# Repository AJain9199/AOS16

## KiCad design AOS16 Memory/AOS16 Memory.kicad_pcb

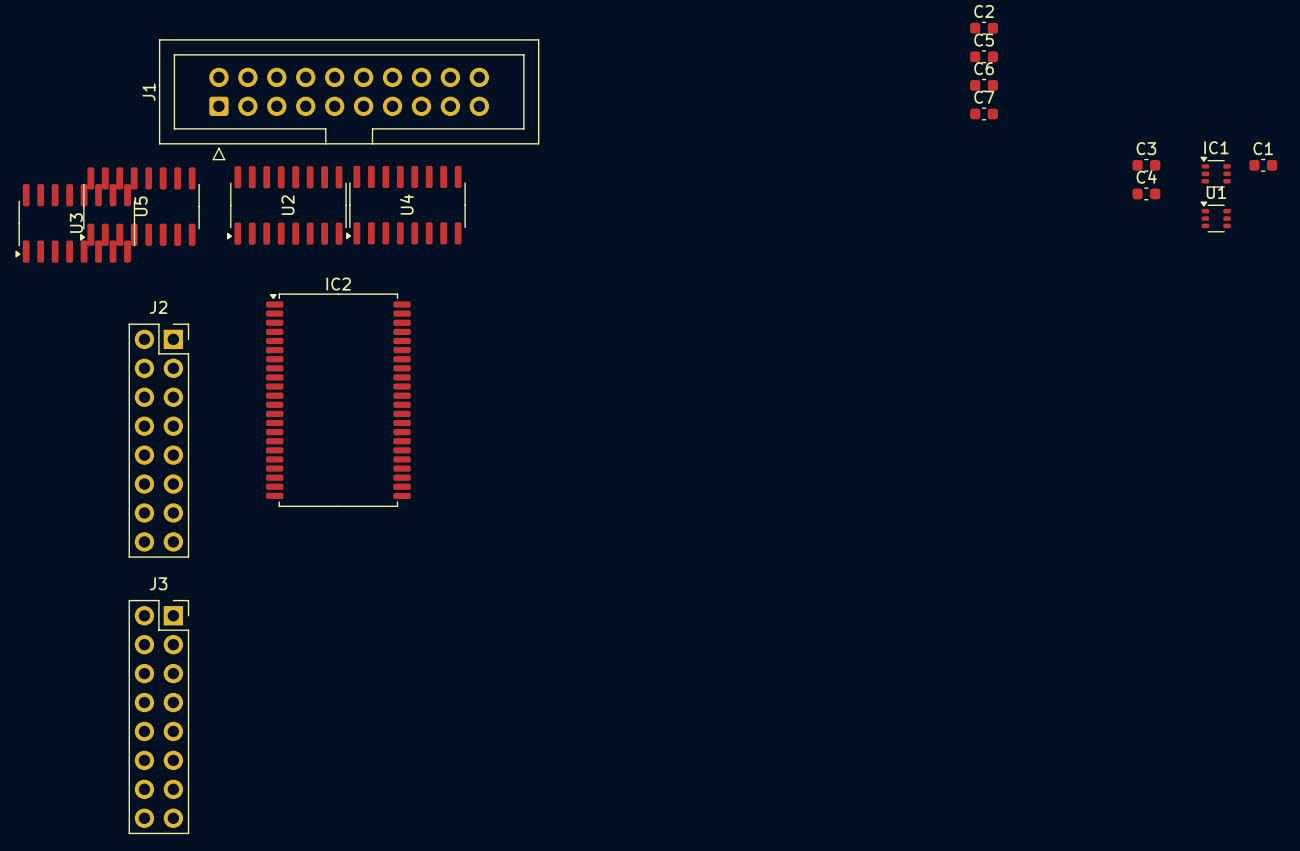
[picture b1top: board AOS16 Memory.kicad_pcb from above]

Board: 2 copper layers, 17 parts (0 on the bottom side), 39 nets, no tracks yet.

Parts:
C1, C2, C3, C4, C5, C6, C7: 0.1uF; C_0603_1608Metric
IC1: SN74AUP2G14DCKR; SOT-363_SC-70-6
IC2: IS61WV3216BLL-12TLI; TSOP-II-44_10.16x18.41mm_P0.8mm
J1: Conn_02x10_Odd_Even; IDC-Header_2x10_P2.54mm_Vertical
J2, J3: Conn_02x08_Top_Bottom; PinSocket_2x08_P2.54mm_Vertical
U1: 4081; SOT-363_SC-70-6
U2, U3, U4, U5: 74HC173; SOIC-16_3.9x9.9mm_P1.27mm

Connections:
/bus_conn/GND: J1.17, J1.19
/ram_chip/~OE: IC2.41 (~OE), U1.3
/register/CLK: J1.18, U2.7 (Cp), U3.7 (Cp), U4.7 (Cp), U5.7 (Cp)
/wordconn1/IN0: IC2.29 (I/O8), J1.1, J3.1, U3.14 (D0)
/wordconn1/IN1: IC2.16 (I/O7), J1.2, J3.2, U3.13 (D1)
/wordconn1/IN2: IC2.30 (I/O9), J1.3, J3.3, U3.12 (D2)
/wordconn1/IN3: IC2.7 (I/O0), J1.4, J3.4, U3.11 (D3)
/wordconn1/IN4: IC2.15 (I/O6), J1.5, J3.5, U5.14 (D0)
/wordconn1/IN5: IC2.8 (I/O1), J1.6, J3.6, U5.13 (D1)
/wordconn1/IN6: IC2.31 (I/O10), J1.7, J3.7, U5.12 (D2)
/wordconn1/IN7: IC2.38 (I/O15), J1.8, J3.8, U5.11 (D3)
/wordconn1/IN8: IC2.14 (I/O5), J1.9, J3.9, U2.14 (D0)
/wordconn1/IN9: IC2.9 (I/O2), J1.10, J3.10, U2.13 (D1)
/wordconn1/IN10: IC2.37 (I/O14), J1.11, J3.11, U2.12 (D2)
/wordconn1/IN11: IC2.32 (I/O11), J1.12, J3.12, U2.11 (D3)
/wordconn1/IN12: IC2.10 (I/O3), J1.13, J3.13, U4.14 (D0)
/wordconn1/IN13: IC2.13 (I/O4), J1.14, J3.14, U4.13 (D1)
/wordconn1/IN14: IC2.35 (I/O12), J1.15, J3.15, U4.12 (D2)
/wordconn1/IN15: IC2.36 (I/O13), J1.16, J3.16, U4.11 (D3)
/wordconn/IN0: IC2.44 (A0), J2.1, U3.3 (Q0)
/wordconn/IN1: IC2.2 (A14), J2.2, U3.4 (Q1)
/wordconn/IN2: IC2.21 (A7), J2.3, U3.5 (Q2)
/wordconn/IN3: IC2.43 (A1), J2.4, U3.6 (Q3)
/wordconn/IN4: IC2.24 (A6), J2.5, U5.3 (Q0)
/wordconn/IN5: IC2.3 (A13), J2.6, U5.4 (Q1)
/wordconn/IN6: IC2.20 (A8), J2.7, U5.5 (Q2)
/wordconn/IN7: IC2.42 (A2), J2.8, U5.6 (Q3)
/wordconn/IN8: IC2.25 (A5), J2.9, U2.3 (Q0)
/wordconn/IN9: IC2.4 (A12), J2.10, U2.4 (Q1)
/wordconn/IN10: IC2.19 (A9), J2.11, U2.5 (Q2)
/wordconn/IN11: IC2.5 (A11), J2.12, U2.6 (Q3)
/wordconn/IN12: IC2.26 (A4), J2.13, U4.3 (Q0)
/wordconn/IN13: IC2.27 (A3), J2.14, U4.4 (Q1)
/wordconn/IN14: IC2.18 (A10), J2.15, U4.5 (Q2)
/wordconn/IN15: IC1.3 (2A), J2.16, U4.6 (Q3)
/~DOUT15: IC1.4 (2Y), U1.1
/~MAI: IC1.6 (1Y), U2.9 (E1), U2.10 (E2), U3.9 (E1), U3.10 (E2), U4.9 (E1), U4.10 (E2), U5.9 (E1), U5.10 (E2)
GND: C1.1, C2.2, C3.2, C4.2, C5.2, C6.2, C7.2, IC1.2 (GND), IC2.6 (~CE), IC2.12 (GND_1), IC2.34 (GND_2), IC2.39 (~LB), IC2.40 (~UB), U2.1 (Oe1), U2.2 (Oe2), U2.8 (GND), U2.15 (Mr), U3.1 (Oe1), U3.2 (Oe2), U3.8 (GND), U3.15 (Mr), U4.1 (Oe1), U4.2 (Oe2), U4.8 (GND), U4.15 (Mr), U5.1 (Oe1), U5.2 (Oe2), U5.8 (GND), U5.15 (Mr)
VCC: C1.2, C2.1, C3.1, C4.1, C5.1, C6.1, C7.1, IC1.5 (VCC), IC2.11 (VDD_1), IC2.33 (VDD_2), U2.16 (VCC), U3.16 (VCC), U4.16 (VCC), U5.16 (VCC)

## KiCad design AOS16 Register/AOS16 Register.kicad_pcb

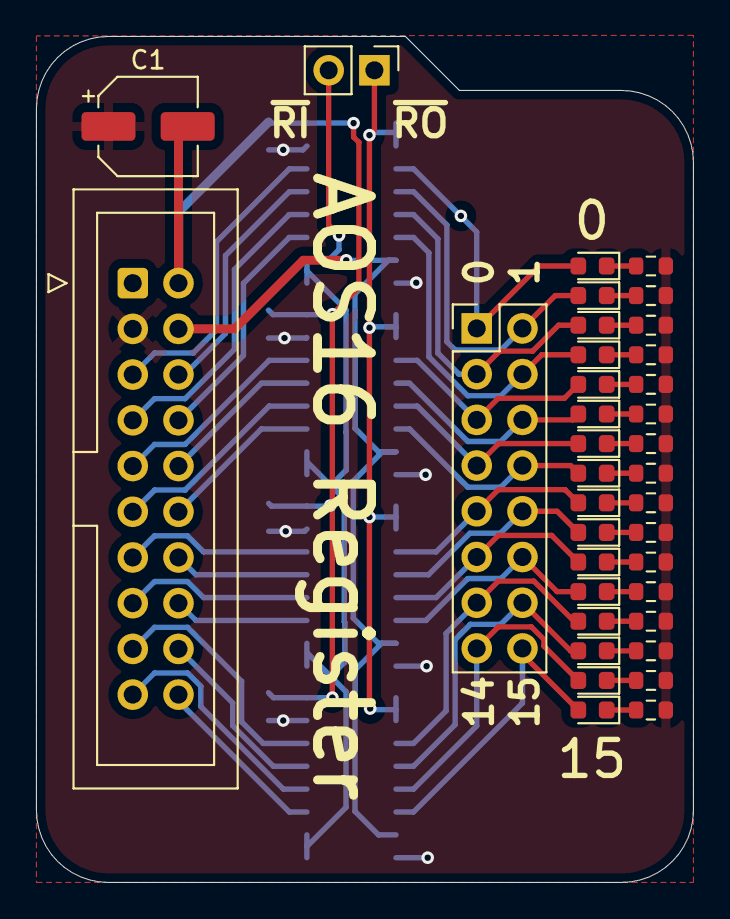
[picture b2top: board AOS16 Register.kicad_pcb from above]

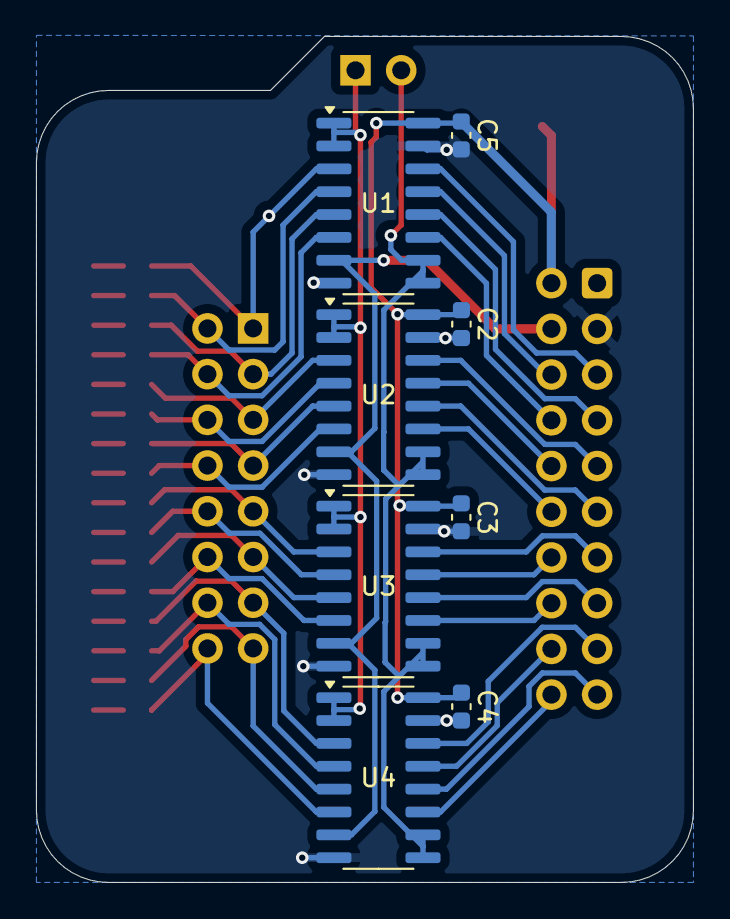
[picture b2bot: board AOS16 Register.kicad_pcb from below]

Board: 2 copper layers, 36.5 x 47.0 mm, 44 parts (8 on the bottom side), 53 nets.

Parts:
C1: 100uF; CP_Elec_5x5.3
C2, C3, C4, C5: 0.1uF; C_0603_1608Metric
D1, D2, D3, D4, D5, D6, D7, D8, D9, D10, D11, D12, D13, D14, D15, D16: LED; LED_0603_1608Metric
J1: Conn_01x02_Pin; PinHeader_1x02_P2.54mm_Vertical
J2: Conn_02x10_Odd_Even; IDC-Header_2x10_P2.54mm_Vertical
J3: Conn_02x08_Top_Bottom; PinHeader_2x08_P2.54mm_Vertical
R1, R2, R3, R4, R5, R6, R7, R8, R9, R10, R11, R12, R13, R14, R15, R16: R_Small; R_0603_1608Metric
U1, U2, U3, U4: 74HC173; SOIC-16_3.9x9.9mm_P1.27mm

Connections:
/CLK: J2.4, U1.7 (Cp), U2.7 (Cp), U3.7 (Cp), U4.7 (Cp)
/DOUT0: D1.2 (A), J3.1, U1.3 (Q0)
/DOUT1: D2.2 (A), J3.2, U1.4 (Q1)
/DOUT2: D3.2 (A), J3.3, U1.5 (Q2)
/DOUT3: D4.2 (A), J3.4, U1.6 (Q3)
/DOUT4: D5.2 (A), J3.5, U2.3 (Q0)
/DOUT5: D6.2 (A), J3.6, U2.4 (Q1)
/DOUT6: D7.2 (A), J3.7, U2.5 (Q2)
/DOUT7: D8.2 (A), J3.8, U2.6 (Q3)
/DOUT8: D9.2 (A), J3.9, U3.3 (Q0)
/DOUT9: D10.2 (A), J3.10, U3.4 (Q1)
/DOUT10: D11.2 (A), J3.11, U3.5 (Q2)
/DOUT11: D12.2 (A), J3.12, U3.6 (Q3)
/DOUT12: D13.2 (A), J3.13, U4.3 (Q0)
/DOUT13: D14.2 (A), J3.14, U4.4 (Q1)
/DOUT14: D15.2 (A), J3.15, U4.5 (Q2)
/DOUT15: D16.2 (A), J3.16, U4.6 (Q3)
/IO0: J2.5, U1.14 (D0)
/IO1: J2.6, U1.13 (D1)
/IO2: J2.7, U1.12 (D2)
/IO3: J2.8, U1.11 (D3)
/IO4: J2.9, U2.14 (D0)
/IO5: J2.10, U2.13 (D1)
/IO6: J2.11, U2.12 (D2)
/IO7: J2.12, U2.11 (D3)
/IO8: J2.13, U3.14 (D0)
/IO9: J2.14, U3.13 (D1)
/IO10: J2.15, U3.12 (D2)
/IO11: J2.16, U3.11 (D3)
/IO12: J2.17, U4.14 (D0)
/IO13: J2.18, U4.13 (D1)
/IO14: J2.19, U4.12 (D2)
/IO15: J2.20, U4.11 (D3)
/~IE: J1.2, U1.9 (E1), U1.10 (E2), U2.9 (E1), U2.10 (E2), U3.9 (E1), U3.10 (E2), U4.9 (E1), U4.10 (E2)
/~OE: J1.1, U1.1 (Oe1), U1.2 (Oe2), U2.1 (Oe1), U2.2 (Oe2), U3.1 (Oe1), U3.2 (Oe2), U4.1 (Oe1), U4.2 (Oe2)
GND: C1.1, C2.2, C3.2, C4.2, C5.2, J2.3, R1.2, R2.2, R3.2, R4.2, R5.2, R6.2, R7.2, R8.2, R9.2, R10.2, R11.2, R12.2, R13.2, R14.2, R15.2, R16.2, U1.8 (GND), U1.15 (Mr), U2.8 (GND), U2.15 (Mr), U3.8 (GND), U3.15 (Mr), U4.8 (GND), U4.15 (Mr)
unnamed: D1.1 (K), R1.1
unnamed: D2.1 (K), R2.1
unnamed: D3.1 (K), R3.1
unnamed: D4.1 (K), R4.1
unnamed: D5.1 (K), R5.1
unnamed: D6.1 (K), R6.1
unnamed: D7.1 (K), R7.1
unnamed: D8.1 (K), R8.1
unnamed: D9.1 (K), R9.1
unnamed: D10.1 (K), R10.1
unnamed: D11.1 (K), R11.1
unnamed: D12.1 (K), R12.1
unnamed: D13.1 (K), R13.1
unnamed: D14.1 (K), R14.1
unnamed: D15.1 (K), R15.1
unnamed: D16.1 (K), R16.1
VCC: C1.2, C2.1, C3.1, C4.1, C5.1, J2.2, U1.16 (VCC), U2.16 (VCC), U3.16 (VCC), U4.16 (VCC)

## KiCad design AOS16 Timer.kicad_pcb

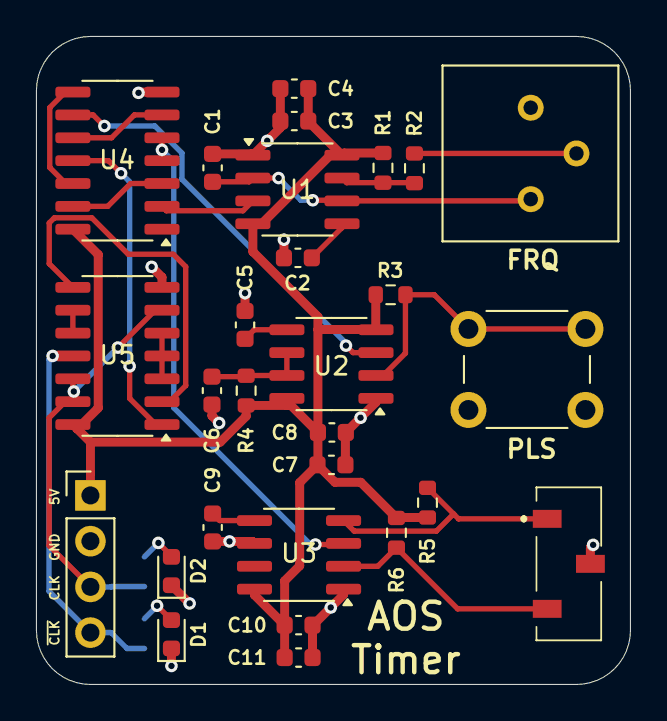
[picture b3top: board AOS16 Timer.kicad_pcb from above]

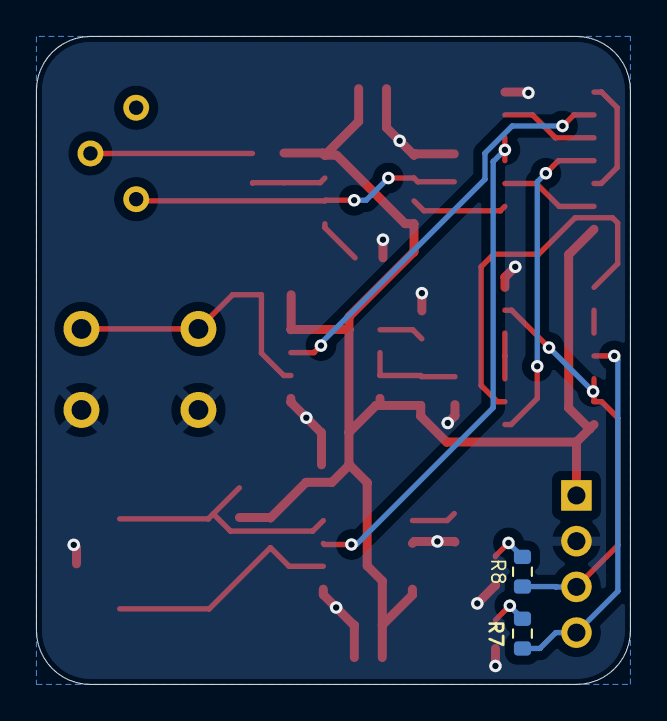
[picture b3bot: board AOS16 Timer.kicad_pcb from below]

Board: 2 copper layers, 33.0 x 36.0 mm, 30 parts (2 on the bottom side), 26 nets.

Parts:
C1, C4, C7, C10: 1µF; C_0603_1608Metric
C2, C5, C9: 0.01µF; C_0603_1608Metric
C3, C6, C8, C11: 0.1µF; C_0603_1608Metric
D1, D2: LED; LED_0603_1608Metric
J1: Conn_01x04_Pin; PinHeader_1x04_P2.54mm_Vertical
R1, R2, R3, R5, R6: 1K; R_0603_1608Metric
R4: 1M; R_0603_1608Metric
R7, R8: 100; R_0603_1608Metric
RV1: 1M; Potentiometer_Bourns_3386P_Vertical
S1: JS102011JCQN
SW1: SW_Push; SW_PUSH_6mm_H5mm
U1, U2, U3: LM555xMM; SOIC-8_3.9x4.9mm_P1.27mm
U4, U5: 7400; SOIC-14_3.9x8.7mm_P1.27mm

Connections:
/HLT: U5.9, U5.10
GND: C1.2, C2.2, C3.2, C4.2, C5.2, C6.2, C7.2, C8.2, C9.2, C10.2, C11.2, D1.1 (K), D2.1 (K), J1.2, S1.2, SW1.1, U1.1 (GND), U2.1 (GND), U3.1 (GND), U3.6 (THR), U4.7 (GND), U5.7 (GND)
unnamed: D1.2 (A), R7.1
unnamed: D2.2 (A), R8.1
unnamed: J1.3, R8.2, U5.6, U5.12, U5.13
unnamed: J1.4, R7.2, U5.11
unnamed: R2.2, RV1.2
unnamed: C2.1, U1.5 (CV)
unnamed: R1.2, R2.1, U1.7 (DIS)
unnamed: U1.3 (Q), U4.2
unnamed: C1.1, RV1.1, U1.2 (TR), U1.6 (THR)
unnamed: C5.1, U2.5 (CV)
unnamed: C6.1, R4.2, U2.6 (THR), U2.7 (DIS)
unnamed: U2.3 (Q), U4.9
unnamed: R3.1, SW1.2, U2.2 (TR)
unnamed: C9.1, U3.5 (CV)
unnamed: U3.3 (Q), U4.1, U4.4, U4.5
unnamed: R5.2, S1.1, U3.4 (R)
unnamed: R6.2, S1.3, U3.2 (TR)
unnamed: U4.6, U4.10
unnamed: U4.11, U5.1
unnamed: U4.8, U4.12
unnamed: U4.3, U4.13
unnamed: U5.2, U5.8
unnamed: U5.3, U5.4, U5.5
VCC: C3.1, C4.1, C7.1, C8.1, C10.1, C11.1, J1.1, R1.1, R3.2, R4.1, R5.1, R6.1, U1.4 (R), U1.8 (VCC), U2.4 (R), U2.8 (VCC), U3.8 (VCC), U4.14 (VCC), U5.14 (VCC)

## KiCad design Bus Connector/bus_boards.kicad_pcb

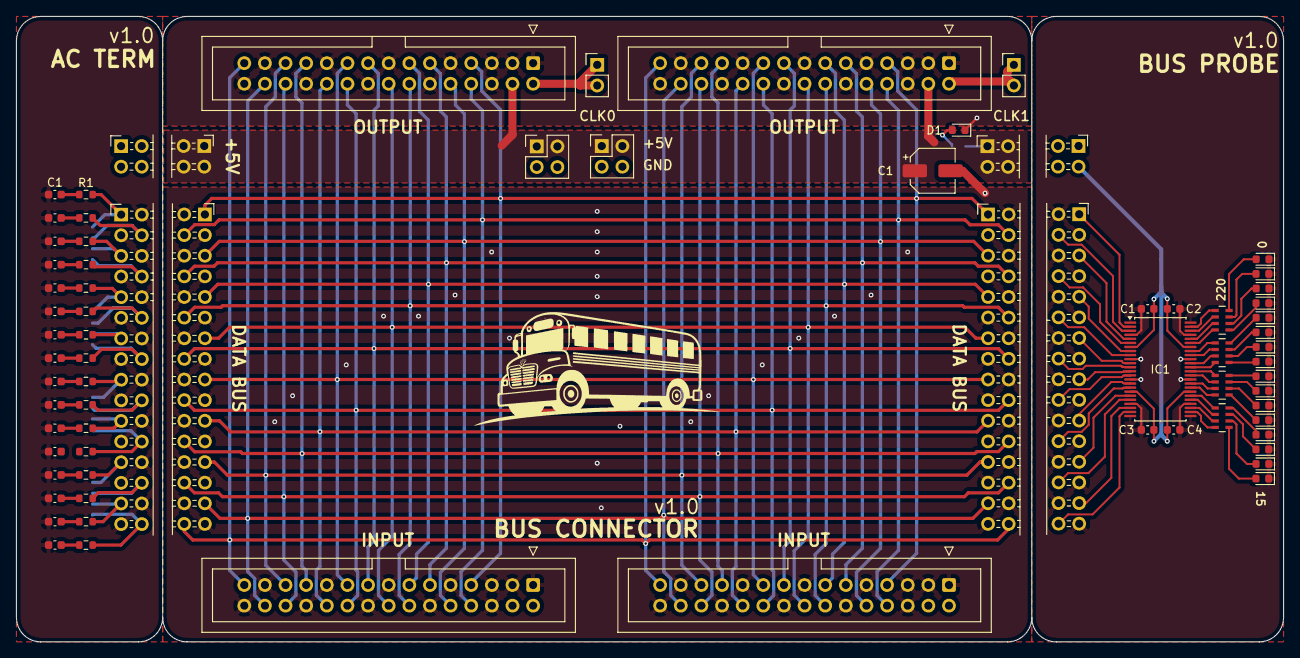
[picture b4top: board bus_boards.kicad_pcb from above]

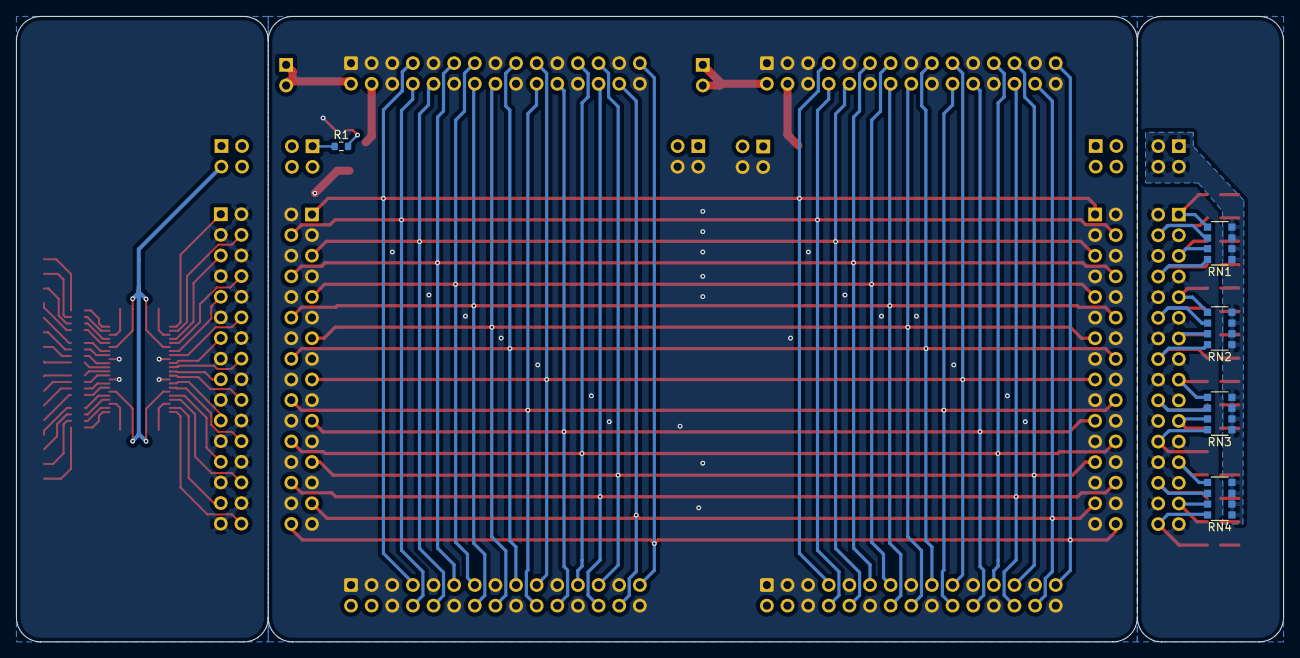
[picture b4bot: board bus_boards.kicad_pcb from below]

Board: 2 copper layers, 156.0 x 77.0 mm, 80 parts (5 on the bottom side), 68 nets.

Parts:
C1, C2, C3, C4#2, C5, C6, C7, C8, C9, C10, C11, C12, C13, C14, C15, C16: 100 pF; C_0603_1608Metric
C1#2: 100uF; CP_Elec_5x5.3
C1#3, C2#2, C3#2, C4: 0.01uF; C_0603_1608Metric
D1: LED; LED_0603_1608Metric
D1#2, D2, D3, D4, D5, D6, D7, D8, D9, D10, D11, D12, D13, D14, D15, D16: LED_Small; LED_0603_1608Metric
IC1: SN74AHCT16245DGGR; TSSOP-48_6.1x12.5mm_P0.5mm
J1, J1#2: Conn_02x16_Odd_Even; PinSocket_2x16_P2.54mm_Horizontal
J1#3, J2: Conn_02x16_Odd_Even; PinHeader_2x16_P2.54mm_Horizontal
J2#2, J4: Conn_02x02_Counter_Clockwise; PinSocket_2x02_P2.54mm_Horizontal
J2#3, J3: Conn_02x02_Counter_Clockwise; PinHeader_2x02_P2.54mm_Horizontal
J5, J6, J7, J8: Conn_02x15_Odd_Even; IDC-Header_2x15_P2.54mm_Vertical
J9, J10: Conn_01x02_Pin; PinHeader_1x02_P2.54mm_Vertical
J11, J12: Conn_02x02_Counter_Clockwise; PinHeader_2x02_P2.54mm_Vertical
R1, R2, R3, R4, R5, R6, R7, R8, R9, R10, R11, R12, R13, R14, R15, R16: 100; R_0603_1608Metric
R1#2: 220; R_0603_1608Metric
RN1, RN2, RN3, RN4: R_Pack04; R_Array_Concave_4x0603
RN1#2, RN2#2, RN3#2, RN4#2: 10k; R_Array_Convex_4x1206

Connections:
+5V: C1#2.1, C1#3.1, C2#2.1, C3#2.1, C4.1, IC1.7 (VCC), IC1.18 (VCC), IC1.31 (VCC), IC1.42 (VCC), J2#2.1, J2#2.2, J2#2.3, J2#2.4, J2#3.1, J2#3.2, J2#3.3, J2#3.4, J3.1, J3.2, J3.3, J3.4, J4.1, J4.2, J4.3, J4.4, J7.4, J8.4, J11.1, J11.2, J12.1, J12.2, R1#2.1, RN1#2.1 (R1.1), RN1#2.2 (R2.1), RN1#2.3 (R3.1), RN1#2.4 (R4.1), RN2#2.1 (R1.1), RN2#2.2 (R2.1), RN2#2.3 (R3.1), RN2#2.4 (R4.1), RN3#2.1 (R1.1), RN3#2.2 (R2.1), RN3#2.3 (R3.1), RN3#2.4 (R4.1), RN4#2.1 (R1.1), RN4#2.2 (R2.1), RN4#2.3 (R3.1), RN4#2.4 (R4.1)
/B0: IC1.47 (A0), RN1.1 (R1.1)
/B1: IC1.46 (A1), RN1.2 (R2.1)
/B2: IC1.44 (A2), RN1.3 (R3.1)
/B3: IC1.43 (A3), RN1.4 (R4.1)
/B4: IC1.41 (A4), RN2.1 (R1.1)
/B5: IC1.40 (A5), RN2.2 (R2.1)
/B6: IC1.38 (A6), RN2.3 (R3.1)
/B7: IC1.37 (A7), RN2.4 (R4.1)
/B8: IC1.36 (A8), RN3.1 (R1.1)
/B9: IC1.35 (A9), RN3.2 (R2.1)
/B10: IC1.33 (A10), RN3.3 (R3.1)
/B11: IC1.32 (A11), RN3.4 (R4.1)
/B12: IC1.30 (A12), RN4.1 (R1.1)
/B13: IC1.29 (A13), RN4.2 (R2.1)
/B14: IC1.27 (A14), RN4.3 (R3.1)
/B15: IC1.26 (A15), RN4.4 (R4.1)
/IO0: IC1.2 (B0), J1.1, J1#2.1, J1#3.1, J2.1, J5.7, J6.7, J7.7, J8.7, R1.1, RN1#2.5 (R4.2)
/IO1: IC1.3 (B1), J1.4, J1#2.4, J1#3.4, J2.4, J5.8, J6.8, J7.8, J8.8, R2.1, RN1#2.6 (R3.2)
/IO2: IC1.5 (B2), J1.5, J1#2.5, J1#3.5, J2.5, J5.10, J6.10, J7.10, J8.10, R3.1, RN1#2.7 (R2.2)
/IO3: IC1.6 (B3), J1.8, J1#2.8, J1#3.8, J2.8, J5.11, J6.11, J7.11, J8.11, R4.1, RN1#2.8 (R1.2)
/IO4: IC1.8 (B4), J1.9, J1#2.9, J1#3.9, J2.9, J5.13, J6.13, J7.13, J8.13, R5.1, RN2#2.5 (R4.2)
/IO5: IC1.9 (B5), J1.12, J1#2.12, J1#3.12, J2.12, J5.14, J6.14, J7.14, J8.14, R6.1, RN2#2.6 (R3.2)
/IO6: IC1.11 (B6), J1.13, J1#2.13, J1#3.13, J2.13, J5.16, J6.16, J7.16, J8.16, R7.1, RN2#2.7 (R2.2)
/IO7: IC1.12 (B7), J1.16, J1#2.16, J1#3.16, J2.16, J5.17, J6.17, J7.17, J8.17, R8.1, RN2#2.8 (R1.2)
/IO8: IC1.13 (B8), J1.17, J1#2.17, J1#3.17, J2.17, J5.19, J6.19, J7.19, J8.19, R9.1, RN3#2.5 (R4.2)
/IO9: IC1.14 (B9), J1.20, J1#2.20, J1#3.20, J2.20, J5.20, J6.20, J7.20, J8.20, R10.1, RN3#2.6 (R3.2)
/IO10: IC1.16 (B10), J1.21, J1#2.21, J1#3.21, J2.21, J5.22, J6.22, J7.22, J8.22, R11.1, RN3#2.7 (R2.2)
/IO11: IC1.17 (B11), J1.24, J1#2.24, J1#3.24, J2.24, J5.23, J6.23, J7.23, J8.23, R12.1, RN3#2.8 (R1.2)
/IO12: IC1.19 (B12), J1.25, J1#2.25, J1#3.25, J2.25, J5.25, J6.25, J7.25, J8.25, R13.1, RN4#2.5 (R4.2)
/IO13: IC1.20 (B13), J1.28, J1#2.28, J1#3.28, J2.28, J5.26, J6.26, J7.26, J8.26, R14.1, RN4#2.6 (R3.2)
/IO14: IC1.22 (B14), J1.29, J1#2.29, J1#3.29, J2.29, J5.28, J6.28, J7.28, J8.28, R15.1, RN4#2.7 (R2.2)
/IO15: IC1.23 (B15), J1.32, J1#2.32, J1#3.32, J2.32, J5.29, J6.29, J7.29, J8.29, R16.1, RN4#2.8 (R1.2)
/bus_conn2/CLK: J7.2, J10.1, J10.2
/bus_conn3/CLK: J8.2, J9.1, J9.2
GND: C1.2, C1#2.2, C1#3.2, C2.2, C2#2.2, C3.2, C3#2.2, C4.2, C4#2.2, C5.2, C6.2, C7.2, C8.2, C9.2, C10.2, C11.2, C12.2, C13.2, C14.2, C15.2, C16.2, D1.1 (K), D1#2.1 (K), D2.1 (K), D3.1 (K), D4.1 (K), D5.1 (K), D6.1 (K), D7.1 (K), D8.1 (K), D9.1 (K), D10.1 (K), D11.1 (K), D12.1 (K), D13.1 (K), D14.1 (K), D15.1 (K), D16.1 (K), IC1.1 (T/~R1), IC1.4 (GND), IC1.10 (GND), IC1.15 (GND), IC1.21 (GND), IC1.24 (T/~R2), IC1.25 (~OE2), IC1.28 (GND), IC1.34 (GND), IC1.39 (GND), IC1.45 (GND), IC1.48 (~OE1), J1.2, J1.3, J1.6, J1.7, J1.10, J1.11, J1.14, J1.15, J1.18, J1.19, J1.22, J1.23, J1.26, J1.27, J1.30, J1.31, J1#2.2, J1#2.3, J1#2.6, J1#2.7, J1#2.10, J1#2.11, J1#2.14, J1#2.15, J1#2.18, J1#2.19, J1#2.22, J1#2.23, J1#2.26, J1#2.27, J1#2.30, J1#2.31, J1#3.2, J1#3.3, J1#3.6, J1#3.7, J1#3.10, J1#3.11, J1#3.14, J1#3.15, J1#3.18, J1#3.19, J1#3.22, J1#3.23, J1#3.26, J1#3.27, J1#3.30, J1#3.31, J2.2, J2.3, J2.6, J2.7, J2.10, J2.11, J2.14, J2.15, J2.18, J2.19, J2.22, J2.23, J2.26, J2.27, J2.30, J2.31, J5.1, J5.3, J5.5, J5.6, J5.9, J5.12, J5.15, J5.18, J5.21, J5.24, J5.27, J5.30, J6.1, J6.3, J6.5, J6.6, J6.9, J6.12, J6.15, J6.18, J6.21, J6.24, J6.27, J6.30, J7.1, J7.3, J7.5, J7.6, J7.9, J7.12, J7.15, J7.18, J7.21, J7.24, J7.27, J7.30, J8.1, J8.3, J8.5, J8.6, J8.9, J8.12, J8.15, J8.18, J8.21, J8.24, J8.27, J8.30, J11.3, J11.4, J12.3, J12.4
unnamed: C1.1, R1.2
unnamed: C2.1, R2.2
unnamed: C3.1, R3.2
unnamed: C4#2.1, R4.2
unnamed: C5.1, R5.2
unnamed: C6.1, R6.2
unnamed: C7.1, R7.2
unnamed: C8.1, R8.2
unnamed: C9.1, R9.2
unnamed: C10.1, R10.2
unnamed: C11.1, R11.2
unnamed: C12.1, R12.2
unnamed: C13.1, R13.2
unnamed: C14.1, R14.2
unnamed: C15.1, R15.2
unnamed: C16.1, R16.2
unnamed: D1.2 (A), D1#2.2 (A), R1#2.2, RN1.8 (R1.2)
unnamed: D2.2 (A), RN1.6 (R3.2)
unnamed: D3.2 (A), RN2.8 (R1.2)
unnamed: D4.2 (A), RN2.6 (R3.2)
unnamed: D5.2 (A), RN3.8 (R1.2)
unnamed: D6.2 (A), RN3.6 (R3.2)
unnamed: D7.2 (A), RN4.8 (R1.2)
unnamed: D8.2 (A), RN4.6 (R3.2)
unnamed: D9.2 (A), RN1.7 (R2.2)
unnamed: D10.2 (A), RN1.5 (R4.2)
unnamed: D11.2 (A), RN2.7 (R2.2)
unnamed: D12.2 (A), RN2.5 (R4.2)
unnamed: D13.2 (A), RN3.7 (R2.2)
unnamed: D14.2 (A), RN3.5 (R4.2)
unnamed: D15.2 (A), RN4.7 (R2.2)
unnamed: D16.2 (A), RN4.5 (R4.2)

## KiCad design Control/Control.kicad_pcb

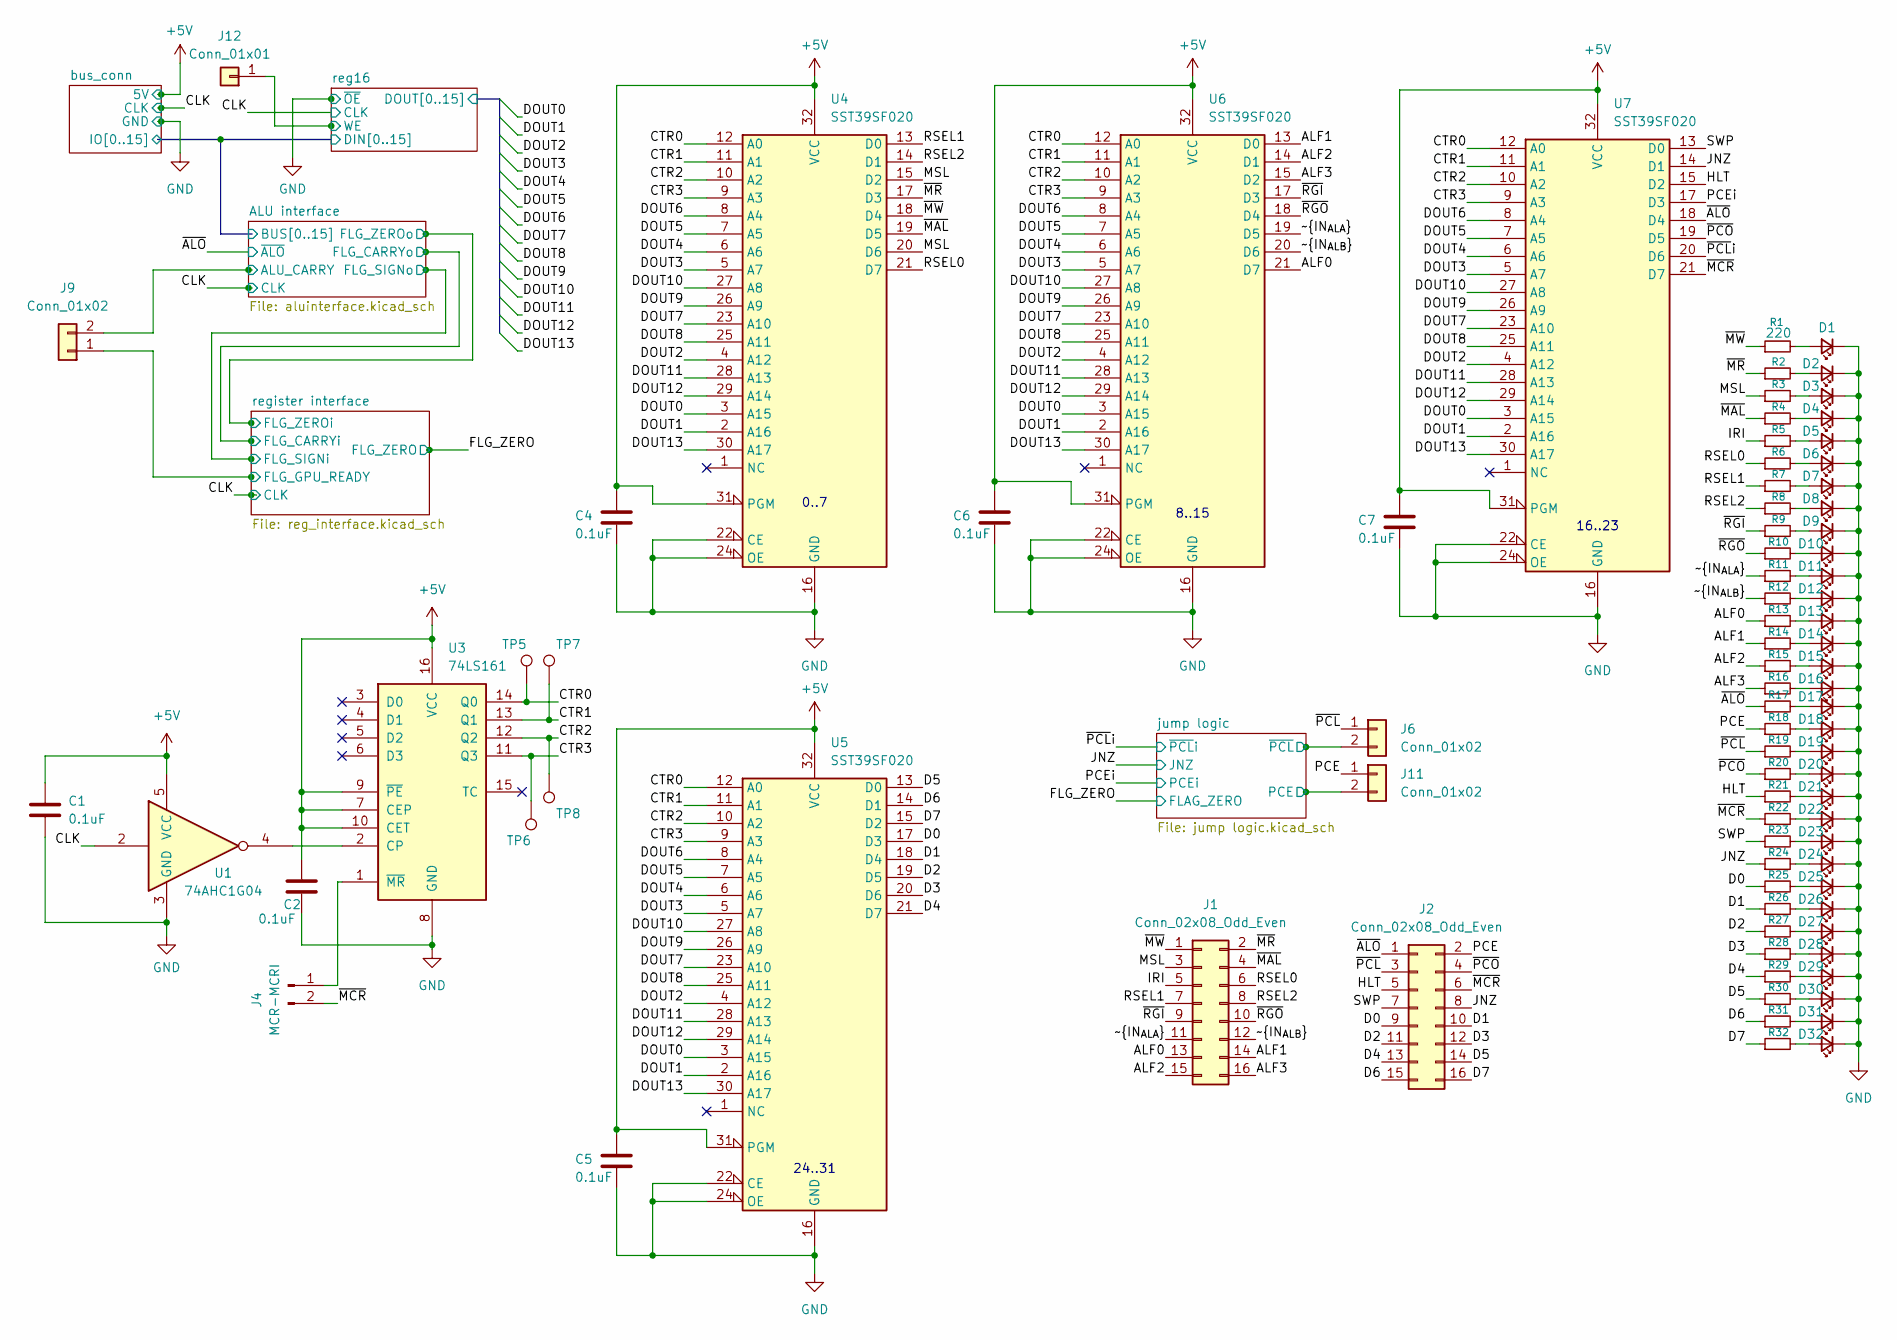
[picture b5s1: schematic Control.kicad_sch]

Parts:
C1, C2, C4, C5, C6, C7: 0.1uF; C_0603_1608Metric
D1, D2, D3, D4, D5, D6, D7, D8, D9, D10, D11, D12, D13, D14, D15, D16, D17, D18, D19, D20, D21, D22, D23, D24, D25, D26, D27, D28, D29, D30, D31, D32: LED_Small; LED_0603_1608Metric
J1, J2: Conn_02x08_Odd_Even; PinHeader_2x08_P2.54mm_Vertical
J4: MCR-MCRI; PinHeader_1x02_P2.54mm_Vertical
J6, J9, J11: Conn_01x02; PinHeader_1x02_P2.54mm_Vertical
J12: Conn_01x01; PinHeader_1x01_P2.54mm_Vertical
R1, R2, R3, R4, R5, R6, R7, R8, R9, R10, R11, R12, R13, R14, R15, R16, R17, R18, R19, R20, R21, R22, R23, R24, R25, R26, R27, R28, R29, R30, R31, R32: 220; R_0603_1608Metric
TP5, TP6, TP7, TP8: TestPoint; TestPoint_Pad_D1.0mm
U1: 74AHC1G04; SOT-23-5
U3: 74LS161; SOIC-16_3.9x9.9mm_P1.27mm
U4, U5, U6, U7: SST39SF020; DIP-32_W15.24mm_Socket

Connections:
+5V: C1.1, C2.1, C4.1, C5.1, C6.1, C7.1, U1.5 (VCC), U3.7 (CEP), U3.9 (~PE), U3.10 (CET), U3.16 (VCC), U4.31 (PGM), U4.32 (VCC), U5.31 (PGM), U5.32 (VCC), U6.31 (PGM), U6.32 (VCC), U7.31 (PGM), U7.32 (VCC); also elsewhere on the board
/ALF0: J1.13, R13.1, U6.21 (D7)
/ALF1: J1.14, R14.1, U6.13 (D0)
/ALF2: J1.15, R15.1, U6.14 (D1)
/ALF3: J1.16, R16.1, U6.15 (D2)
/ALU interface/ALU_CARRY: J9.2; also elsewhere on the board
/CLK: U1.2; also elsewhere on the board
/CTR0: TP5.1, U3.14 (Q0), U4.12 (A0), U5.12 (A0), U6.12 (A0), U7.12 (A0)
/CTR1: TP7.1, U3.13 (Q1), U4.11 (A1), U5.11 (A1), U6.11 (A1), U7.11 (A1)
/CTR2: TP8.1, U3.12 (Q2), U4.10 (A2), U5.10 (A2), U6.10 (A2), U7.10 (A2)
/CTR3: TP6.1, U3.11 (Q3), U4.9 (A3), U5.9 (A3), U6.9 (A3), U7.9 (A3)
/D0: J2.9, R25.1, U5.17 (D3)
/D1: J2.10, R26.1, U5.18 (D4)
/D2: J2.11, R27.1, U5.19 (D5)
/D3: J2.12, R28.1, U5.20 (D6)
/D4: J2.13, R29.1, U5.21 (D7)
/D5: J2.14, R30.1, U5.13 (D0)
/D6: J2.15, R31.1, U5.14 (D1)
/D7: J2.16, R32.1, U5.15 (D2)
/HLT: J2.5, R21.1, U7.15 (D2)
/IRI: J1.5, R5.1
/JNZ: J2.8, R24.1, U7.14 (D1); also elsewhere on the board
/MSL: J1.3, R3.1, U4.15 (D2), U4.20 (D6)
/PCEi: U7.17 (D3); also elsewhere on the board
/RSEL0: J1.6, R6.1, U4.21 (D7)
/RSEL1: J1.7, R7.1, U4.13 (D0)
/RSEL2: J1.8, R8.1, U4.14 (D1)
/SWP: J2.7, R23.1, U7.13 (D0)
/jump logic/PCE: J11.2; also elsewhere on the board
/jump logic/~PCL: J6.2; also elsewhere on the board
/reg16/DOUT0: U4.3 (A15), U5.3 (A15), U6.3 (A15), U7.3 (A15); also elsewhere on the board
/reg16/DOUT1: U4.2 (A16), U5.2 (A16), U6.2 (A16), U7.2 (A16); also elsewhere on the board
/reg16/DOUT2: U4.4 (A12), U5.4 (A12), U6.4 (A12), U7.4 (A12); also elsewhere on the board
/reg16/DOUT3: U4.5 (A7), U5.5 (A7), U6.5 (A7), U7.5 (A7); also elsewhere on the board
/reg16/DOUT4: U4.6 (A6), U5.6 (A6), U6.6 (A6), U7.6 (A6); also elsewhere on the board
/reg16/DOUT5: U4.7 (A5), U5.7 (A5), U6.7 (A5), U7.7 (A5); also elsewhere on the board
/reg16/DOUT6: U4.8 (A4), U5.8 (A4), U6.8 (A4), U7.8 (A4); also elsewhere on the board
/reg16/DOUT7: U4.23 (A10), U5.23 (A10), U6.23 (A10), U7.23 (A10); also elsewhere on the board
/reg16/DOUT8: U4.25 (A11), U5.25 (A11), U6.25 (A11), U7.25 (A11); also elsewhere on the board
/reg16/DOUT9: U4.26 (A9), U5.26 (A9), U6.26 (A9), U7.26 (A9); also elsewhere on the board
/reg16/DOUT10: U4.27 (A8), U5.27 (A8), U6.27 (A8), U7.27 (A8); also elsewhere on the board
/reg16/DOUT11: U4.28 (A13), U5.28 (A13), U6.28 (A13), U7.28 (A13); also elsewhere on the board
/reg16/DOUT12: U4.29 (A14), U5.29 (A14), U6.29 (A14), U7.29 (A14); also elsewhere on the board
/reg16/DOUT13: U4.30 (A17), U5.30 (A17), U6.30 (A17), U7.30 (A17); also elsewhere on the board
/reg16/WE: J12.1; also elsewhere on the board
/register interface/FLG_GPU_READY: J9.1; also elsewhere on the board
/~ALO: J2.1, R17.1, U7.18 (D4); also elsewhere on the board
/~IN_{ALA}: J1.11, R11.1, U6.19 (D5)
/~IN_{ALB}: J1.12, R12.1, U6.20 (D6)
/~MAL: J1.4, R4.1, U4.19 (D5)
/~MCR: J2.6, J4.2, R22.1, U7.21 (D7)
/~MR: J1.2, R2.1, U4.17 (D3)
/~MW: J1.1, R1.1, U4.18 (D4)
/~PCL: J2.3, J6.1, R19.1
/~PCLi: U7.20 (D6); also elsewhere on the board
/~RGI: J1.9, R9.1, U6.17 (D3)
/~RGO: J1.10, R10.1, U6.18 (D4)
GND: C1.2, C2.2, C4.2, C5.2, C6.2, C7.2, D1.1 (K), D2.1 (K), D3.1 (K), D4.1 (K), D5.1 (K), D6.1 (K), D7.1 (K), D8.1 (K), D9.1 (K), D10.1 (K), D11.1 (K), D12.1 (K), D13.1 (K), D14.1 (K), D15.1 (K), D16.1 (K), D17.1 (K), D18.1 (K), D19.1 (K), D20.1 (K), D21.1 (K), D22.1 (K), D23.1 (K), D24.1 (K), D25.1 (K), D26.1 (K), D27.1 (K), D28.1 (K), D29.1 (K), D30.1 (K), D31.1 (K), D32.1 (K), U1.3 (GND), U3.8 (GND), U4.16 (GND), U4.22 (CE), U4.24 (OE), U5.16 (GND), U5.22 (CE), U5.24 (OE), U6.16 (GND), U6.22 (CE), U6.24 (OE), U7.16 (GND), U7.22 (CE), U7.24 (OE); also elsewhere on the board
unnamed: D1.2 (A), R1.2
unnamed: D2.2 (A), R2.2
unnamed: D3.2 (A), R3.2
unnamed: D4.2 (A), R4.2
unnamed: D5.2 (A), R5.2
unnamed: D6.2 (A), R6.2
unnamed: D7.2 (A), R7.2
unnamed: D8.2 (A), R8.2
unnamed: D9.2 (A), R9.2
unnamed: D10.2 (A), R10.2
unnamed: D11.2 (A), R11.2
unnamed: D12.2 (A), R12.2
unnamed: D13.2 (A), R13.2
unnamed: D14.2 (A), R14.2
unnamed: D15.2 (A), R15.2
unnamed: D16.2 (A), R16.2
unnamed: D17.2 (A), R17.2
unnamed: D18.2 (A), R18.2
unnamed: D19.2 (A), R19.2
unnamed: D20.2 (A), R20.2
unnamed: D21.2 (A), R21.2
unnamed: D22.2 (A), R22.2
unnamed: D23.2 (A), R23.2
unnamed: D24.2 (A), R24.2
unnamed: D25.2 (A), R25.2
unnamed: D26.2 (A), R26.2
unnamed: D27.2 (A), R27.2
unnamed: D28.2 (A), R28.2
unnamed: D29.2 (A), R29.2
unnamed: D30.2 (A), R30.2
unnamed: D31.2 (A), R31.2
unnamed: D32.2 (A), R32.2
unnamed: J4.1, U3.1 (~MR)
unnamed: U1.4, U3.2 (CP)

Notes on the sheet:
16..23
24..31
0..7
8..15

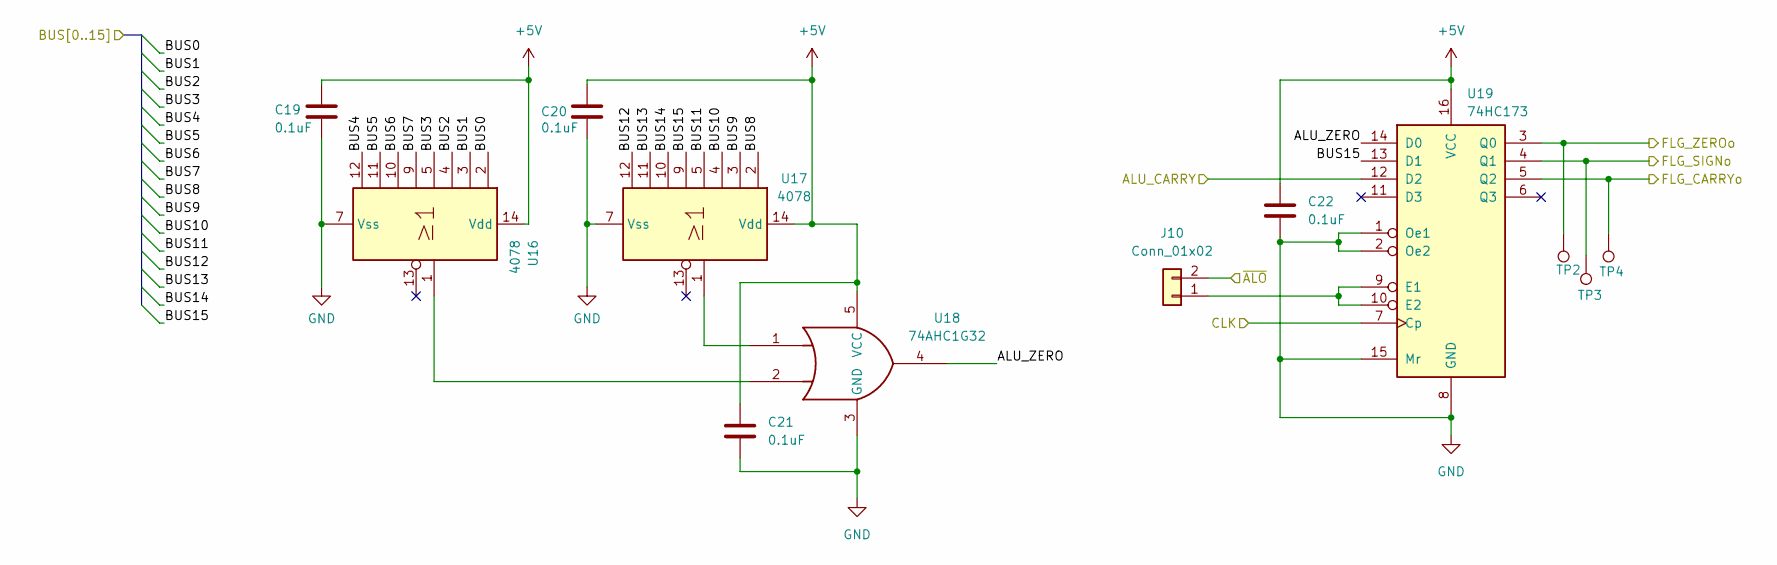
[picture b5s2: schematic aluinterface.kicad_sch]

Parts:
C19, C20, C21, C22: 0.1uF; C_0603_1608Metric
J10: Conn_01x02; PinHeader_1x02_P2.54mm_Vertical
TP2, TP3, TP4: TestPoint; TestPoint_Pad_D1.0mm
U16, U17: 4078; SOIC-14_3.9x8.7mm_P1.27mm
U18: 74AHC1G32; SOT-23-5
U19: 74HC173; SOIC-16_3.9x9.9mm_P1.27mm

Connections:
+5V: C19.1, C20.1, C21.1, C22.1, U16.14 (Vdd), U17.14 (Vdd), U18.5 (VCC), U19.16 (VCC); also elsewhere on the board
/ALU interface/ALU_CARRY: U19.12 (D2); also elsewhere on the board
/ALU interface/ALU_ZERO: U18.4, U19.14 (D0)
/ALU interface/BUS0: U16.2; also elsewhere on the board
/ALU interface/BUS1: U16.3; also elsewhere on the board
/ALU interface/BUS2: U16.4; also elsewhere on the board
/ALU interface/BUS3: U16.5; also elsewhere on the board
/ALU interface/BUS4: U16.12; also elsewhere on the board
/ALU interface/BUS5: U16.11; also elsewhere on the board
/ALU interface/BUS6: U16.10; also elsewhere on the board
/ALU interface/BUS7: U16.9; also elsewhere on the board
/ALU interface/BUS8: U17.2; also elsewhere on the board
/ALU interface/BUS9: U17.3; also elsewhere on the board
/ALU interface/BUS10: U17.4; also elsewhere on the board
/ALU interface/BUS11: U17.5; also elsewhere on the board
/ALU interface/BUS12: U17.12; also elsewhere on the board
/ALU interface/BUS13: U17.11; also elsewhere on the board
/ALU interface/BUS14: U17.10; also elsewhere on the board
/ALU interface/BUS15: U17.9, U19.13 (D1); also elsewhere on the board
/ALU interface/FLG_CARRYo: TP4.1, U19.5 (Q2); also elsewhere on the board
/ALU interface/FLG_SIGNo: TP3.1, U19.4 (Q1); also elsewhere on the board
/ALU interface/FLG_ZEROo: TP2.1, U19.3 (Q0); also elsewhere on the board
/CLK: U19.7 (Cp); also elsewhere on the board
/~ALO: J10.2; also elsewhere on the board
GND: C19.2, C20.2, C21.2, C22.2, U16.7 (Vss), U17.7 (Vss), U18.3 (GND), U19.1 (Oe1), U19.2 (Oe2), U19.8 (GND), U19.15 (Mr); also elsewhere on the board
unnamed: J10.1, U19.9 (E1), U19.10 (E2)
unnamed: U16.1, U18.2
unnamed: U17.1, U18.1

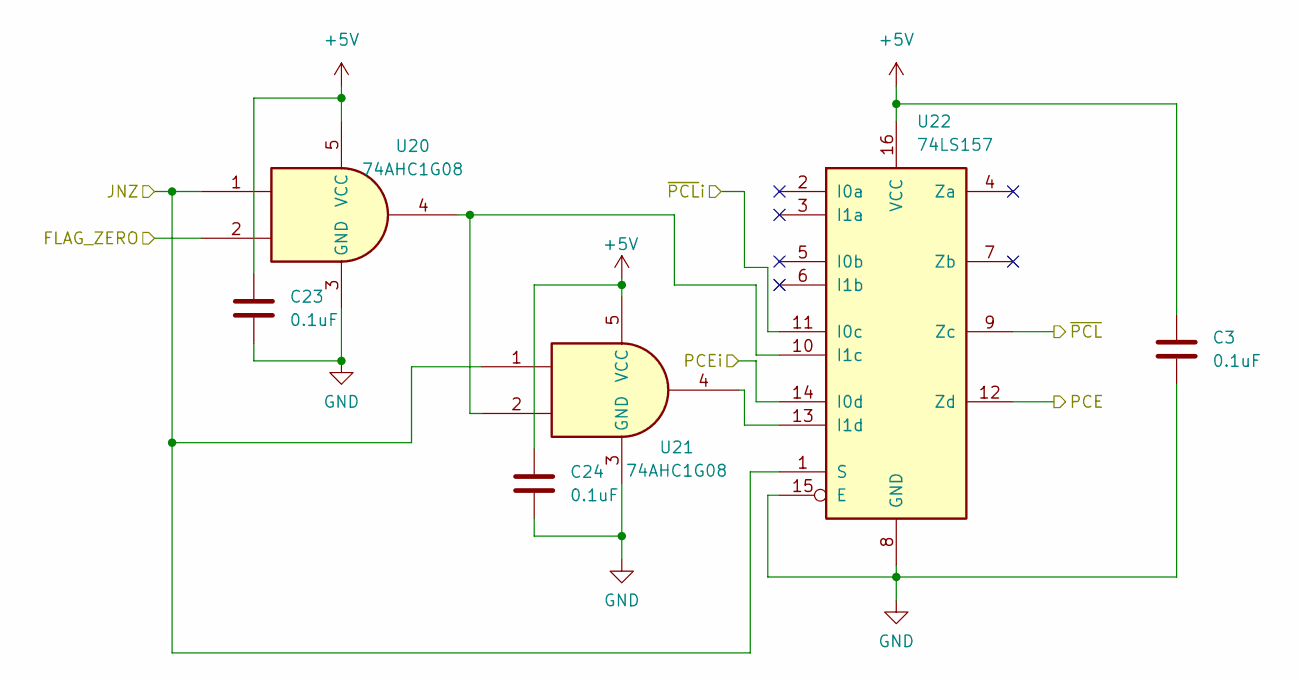
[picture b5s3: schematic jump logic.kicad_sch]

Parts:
C3, C23, C24: 0.1uF; C_0603_1608Metric
U20, U21: 74AHC1G08; SOT-23-5
U22: 74LS157; SOIC-16_3.9x9.9mm_P1.27mm

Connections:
+5V: C3.1, C23.1, C24.1, U20.5 (VCC), U21.5 (VCC), U22.16 (VCC); also elsewhere on the board
/FLG_ZERO: U20.2; also elsewhere on the board
/JNZ: U20.1, U21.1, U22.1 (S); also elsewhere on the board
/PCEi: U22.14 (I0d); also elsewhere on the board
/jump logic/PCE: U22.12 (Zd); also elsewhere on the board
/jump logic/~PCL: U22.9 (Zc); also elsewhere on the board
/~PCLi: U22.11 (I0c); also elsewhere on the board
GND: C3.2, C23.2, C24.2, U20.3 (GND), U21.3 (GND), U22.8 (GND), U22.15 (E); also elsewhere on the board
unnamed: U20.4, U21.2, U22.10 (I1c)
unnamed: U21.4, U22.13 (I1d)

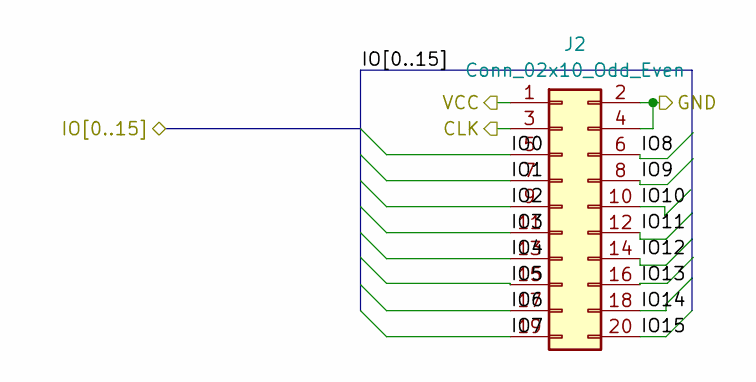
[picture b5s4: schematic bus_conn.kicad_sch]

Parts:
J2: Conn_02x10_Odd_Even; IDC-Header_2x10_P2.54mm_Vertical

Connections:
/D0: J2.9; also elsewhere on the board
/D1: J2.10; also elsewhere on the board
/D2: J2.11; also elsewhere on the board
/D3: J2.12; also elsewhere on the board
/D4: J2.13; also elsewhere on the board
/D5: J2.14; also elsewhere on the board
/D6: J2.15; also elsewhere on the board
/D7: J2.16; also elsewhere on the board
/HLT: J2.5; also elsewhere on the board
/JNZ: J2.8; also elsewhere on the board
/SWP: J2.7; also elsewhere on the board
/~ALO: J2.1; also elsewhere on the board
/~MCR: J2.6; also elsewhere on the board
/~PCL: J2.3; also elsewhere on the board
